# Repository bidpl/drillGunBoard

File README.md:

# 12V Motor Testing Rig

Code for FRC control board. Manual control FRC motors and air compressor.

We used 12v drills to power 12v FRC motors, (CIMs, BAGs, etc) by removing drill spindle and connecting to motor leads. However, it can not supply large amounts of power. It can not drive Neo motors due to their brushless nature. 

This code is for a meant for a test rig that take a pot input and controls PWM motor controlers (Talon SRXs and Spark Maxes are used in this build).

Features:
Control multiple motors (up to 4) (Control moudes v1.1 and v1.2 have support for 5)
LCD readout for motor power

Documentation is a bit scuffed, I only used the repo while developing the first version (v1.0), didn't for later iterations (v1.1/1.2)

v1.0 was based on an arduino uno with regular potentiometers. The arduino by itself was limited to Talon SRXs since it could not generate a stable enough PWM signal for the Spark Max. This version used regular pin headers and cheap dupont wires so it suffered some durability issues (connections were terrible, shaking the testing rig could disconnect parts).

v1.1/1.2 is uses a custom control module (based on an ATMEGA32P, programs exactly like an UNO) that has an additional PWM driver chip (PCA9685). This chip can generate a proper 50hz PWM signal so it can control Spark Maxes as well. This version also uses locking connectors (JST-XH between input modules and the control module, Molex SL connectors for control module to motor controllers).

## PCB Modules

## Testing Rig (The Bomb, name inspired from Die Hard with a Vengeance)

## Change Log
Input Module v1.1:
- Switched from rotate to linear potentiometer
- Switched from horizontal to vertical PCB shape

Control Module v1.2:
- Fixed PCA9685 CE signal (supposed to be active low, was tied high in prev version)

Control Module v1.1:
- Moved from arduino to custom PCB
- Added PCA9685 as PWM signal generator, arduino couldn't get a clean enough PWM signal for some motor controllers (Controlling the LCD delayed the signal too much)
- Switched from loose dupont wire to locking Molex-SL and JST-XH connectors

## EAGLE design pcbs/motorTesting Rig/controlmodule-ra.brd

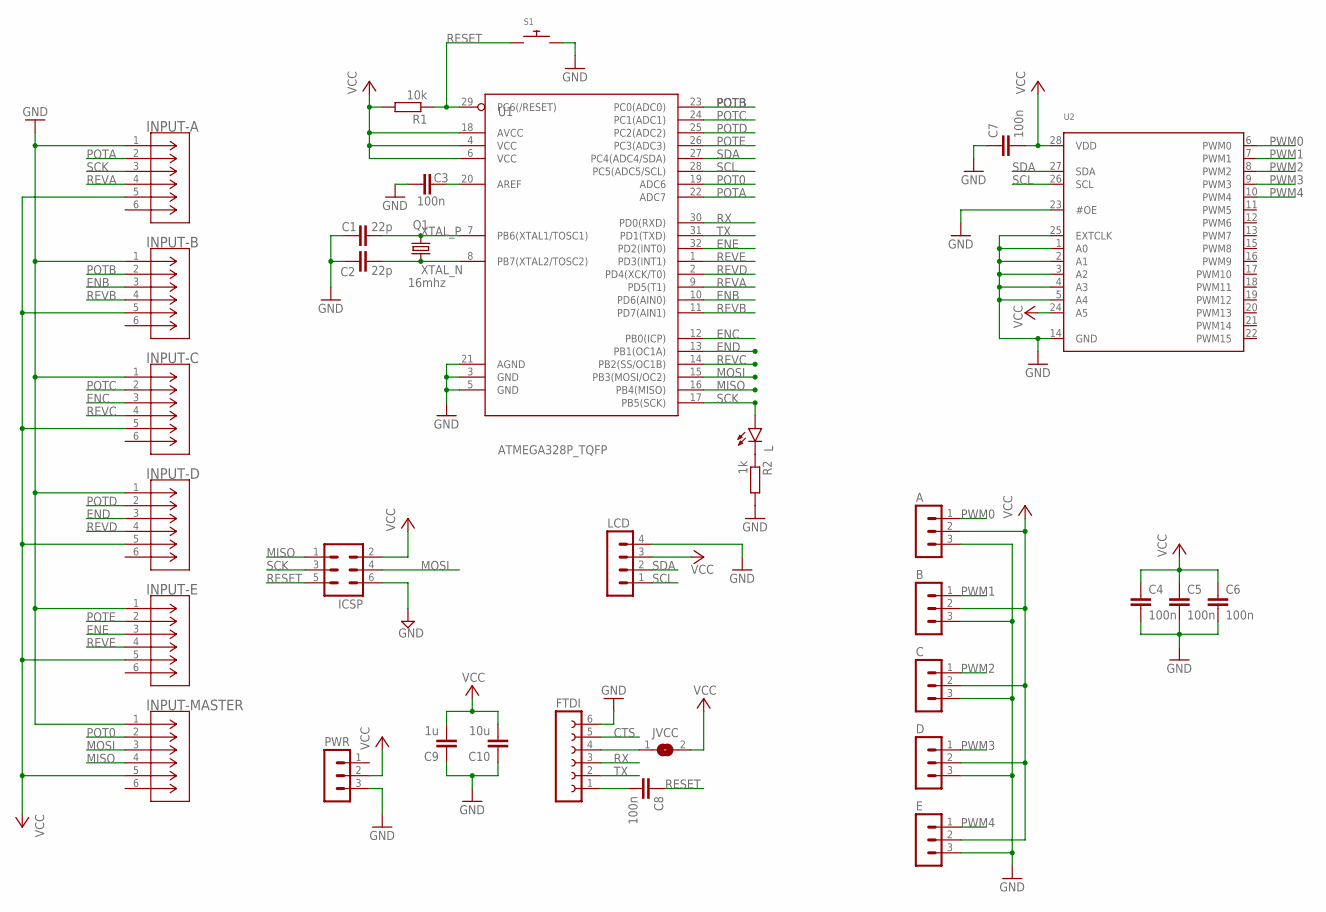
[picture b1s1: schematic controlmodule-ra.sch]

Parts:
A: MOLEX-SL-3PIN-RA-BOARD-LOCK
B: MOLEX-SL-3PIN-RA-BOARD-LOCK
C: MOLEX-SL-3PIN-RA-BOARD-LOCK
C1, C2: 22p; C0805
C3, C4, C5, C6, C7, C8: 100n; C0805
C9: 1u; C0805
C10: 10u; C0805
D: MOLEX-SL-3PIN-RA-BOARD-LOCK
E: MOLEX-SL-3PIN-RA-BOARD-LOCK
FTDI: FE06-1; FE06
ICSP: MA03-2
INPUT-A: B6B-PH-K-S(LF)(SN)-JST; CONN_B6B-PH-K-S_JST
INPUT-B: B6B-PH-K-S(LF)(SN)-JST; CONN_B6B-PH-K-S_JST
INPUT-C: B6B-PH-K-S(LF)(SN)-JST; CONN_B6B-PH-K-S_JST
INPUT-D: B6B-PH-K-S(LF)(SN)-JST; CONN_B6B-PH-K-S_JST
INPUT-E: B6B-PH-K-S(LF)(SN)-JST; CONN_B6B-PH-K-S_JST
INPUT-MASTER: B6B-PH-K-S(LF)(SN)-JST; CONN_B6B-PH-K-S_JST
JVCC: SJ
L: LEDCHIP-LED0805; CHIP-LED0805
LCD: MOLEX-SL-4PIN-RA-BOARD-LOCK
PWR: MOLEX-SL-3PIN-RA-BOARD-LOCK
Q1: 16mhz; HC49UP
R1: 10k; R0805
R2: 1k; R0805
S1: 3X4MM-PUHSBUTTON; 3X4MM-PUSHBUTTON
U1: ATMEGA328P_TQFP; TQFP32-08
U2: PCA9685; TSSOP28

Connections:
CTS: FTDI.5
ENB: INPUT-B.3, U1.10 (PD6(AIN0))
ENC: INPUT-C.3, U1.12 (PB0(ICP))
END: INPUT-D.3, U1.13 (PB1(OC1A))
ENE: INPUT-E.3, U1.32 (PD2(INT0))
GND: A.3, B.3, C.3, C1.1, C2.1, C3.2, C4.2, C5.2, C6.2, C7.1, C9.1, C10.1, D.3, E.3, FTDI.6, ICSP.6, INPUT-A.1, INPUT-B.1, INPUT-C.1, INPUT-D.1, INPUT-E.1, INPUT-MASTER.1, LCD.4, PWR.3, R2.2, S1.P$2, U1.3 (GND), U1.5 (GND), U1.21 (AGND), U2.1 (A0), U2.2 (A1), U2.3 (A2), U2.4 (A3), U2.5 (A4), U2.14 (GND), U2.23 (#OE), U2.25 (EXTCLK)
MISO: ICSP.1, INPUT-MASTER.4, U1.16 (PB4(MISO))
MOSI: ICSP.4, INPUT-MASTER.3, U1.15 (PB3(MOSI/OC2))
unnamed: FTDI.4, JVCC.1
unnamed: L.C, R2.1
unnamed: C3.1, U1.20 (AREF)
unnamed: C8.2, FTDI.1
POT0: INPUT-MASTER.2, U1.19 (ADC6)
POTA: INPUT-A.2, U1.22 (ADC7)
POTB: INPUT-B.2, U1.23 (PC0(ADC0))
POTC: INPUT-C.2, U1.24 (PC1(ADC1))
POTD: INPUT-D.2, U1.25 (PC2(ADC2))
POTE: INPUT-E.2, U1.26 (PC3(ADC3))
PWM0: A.1, U2.6 (PWM0)
PWM1: B.1, U2.7 (PWM1)
PWM2: C.1, U2.8 (PWM2)
PWM3: D.1, U2.9 (PWM3)
PWM4: E.1, U2.10 (PWM4)
RESET: C8.1, ICSP.5, R1.1, S1.P$1, U1.29 (PC6(/RESET))
REVA: INPUT-A.4, U1.9 (PD5(T1))
REVB: INPUT-B.4, U1.11 (PD7(AIN1))
REVC: INPUT-C.4, U1.14 (PB2(SS/OC1B))
REVD: INPUT-D.4, U1.2 (PD4(XCK/T0))
REVE: INPUT-E.4, U1.1 (PD3(INT1))
RX: FTDI.3, U1.30 (PD0(RXD))
SCK: ICSP.3, INPUT-A.3, L.A, U1.17 (PB5(SCK))
SCL: LCD.1, U1.28 (PC5(ADC5/SCL)), U2.26 (SCL)
SDA: LCD.2, U1.27 (PC4(ADC4/SDA)), U2.27 (SDA)
TX: FTDI.2, U1.31 (PD1(TXD))
VCC: A.2, B.2, C.2, C4.1, C5.1, C6.1, C7.2, C9.2, C10.2, D.2, E.2, ICSP.2, INPUT-A.5, INPUT-B.5, INPUT-C.5, INPUT-D.5, INPUT-E.5, INPUT-MASTER.5, JVCC.2, LCD.3, PWR.2, R1.2, U1.4 (VCC), U1.6 (VCC), U1.18 (AVCC), U2.24 (A5), U2.28 (VDD)
XTAL_N: C2.2, Q1.1, U1.8 (PB7(XTAL2/TOSC2))
XTAL_P: C1.2, Q1.2, U1.7 (PB6(XTAL1/TOSC1))

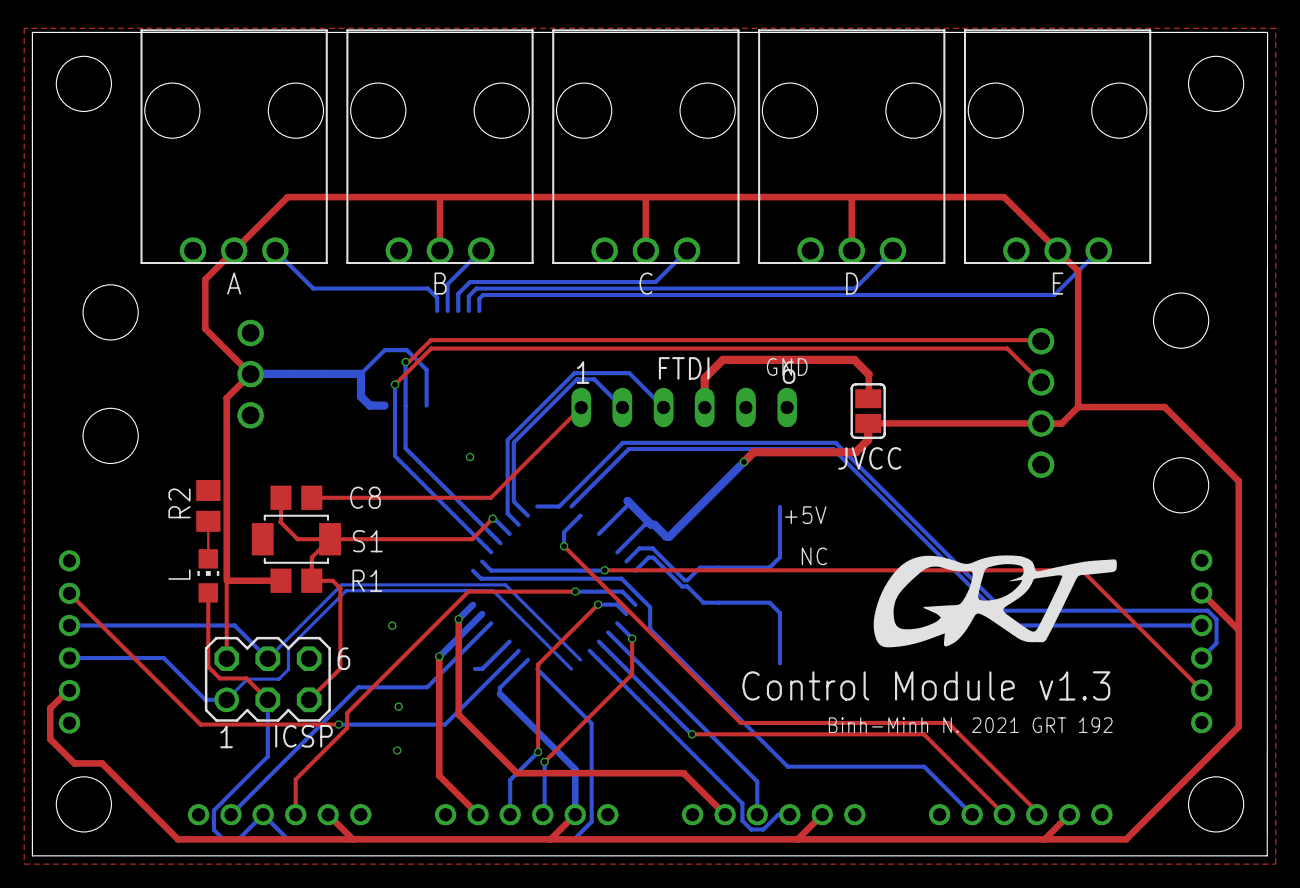
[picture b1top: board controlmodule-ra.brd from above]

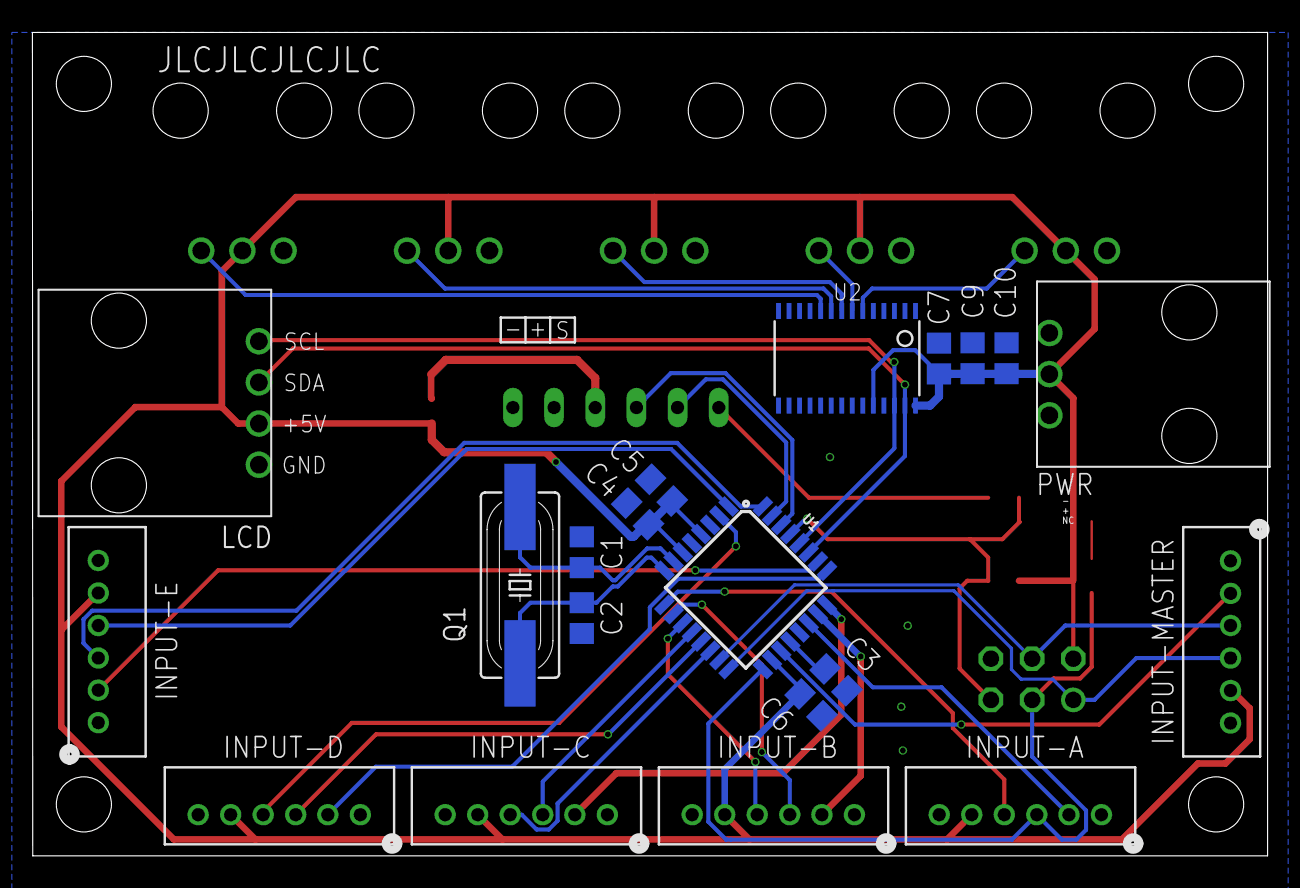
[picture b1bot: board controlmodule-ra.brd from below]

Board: 2 copper layers, 76.2 x 50.8 mm, 33 parts (20 on the bottom side), 36 nets.

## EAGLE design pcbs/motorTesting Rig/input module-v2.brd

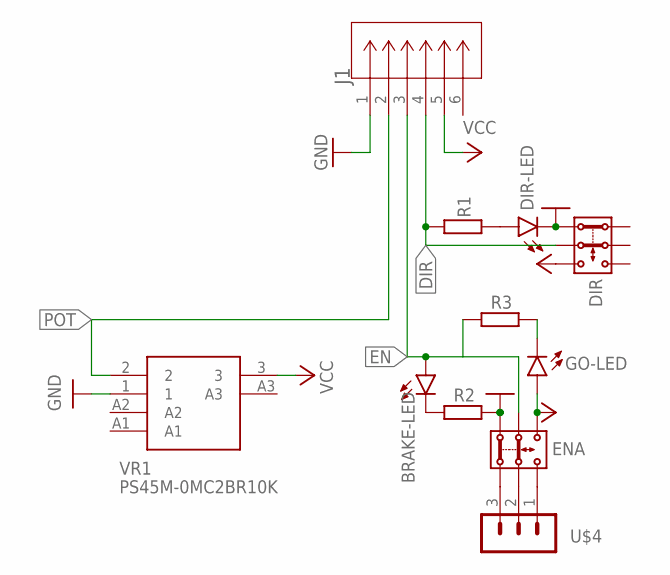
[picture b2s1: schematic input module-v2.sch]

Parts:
BRAKE-LED: LED5MM
DIR: DPDT-PUSHBUTTON; 7MM*7MM
DIR-LED: LED5MM
ENA: DPDT-PUSHBUTTON; 7MM*7MM
GO-LED: LED5MM
J1: B6B-PH-K-S(LF)(SN)-JST; CONN_B6B-PH-K-S_JST
R1, R2, R3: R-EU_0207/10; 0207/10
U$4: MALE-HEADER-3PIN; MA03-1
VR1: PS45M-0MC2BR10K; PS45M0MC2BR10K

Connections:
DIR: DIR.2, J1.4, R1.1
EN: BRAKE-LED.A, ENA.5, J1.3, R3.1
GND: DIR.1, DIR-LED.K (C), ENA.6, J1.1, R2.2, VR1.1
unnamed: DIR-LED.A, R1.2
unnamed: ENA.3, U$4.1
unnamed: ENA.2, U$4.2
unnamed: ENA.1, U$4.3
unnamed: BRAKE-LED.K (C), R2.1
unnamed: GO-LED.K (C), R3.2
POT: J1.2, VR1.2
VCC: DIR.3, ENA.4, GO-LED.A, J1.5, VR1.3

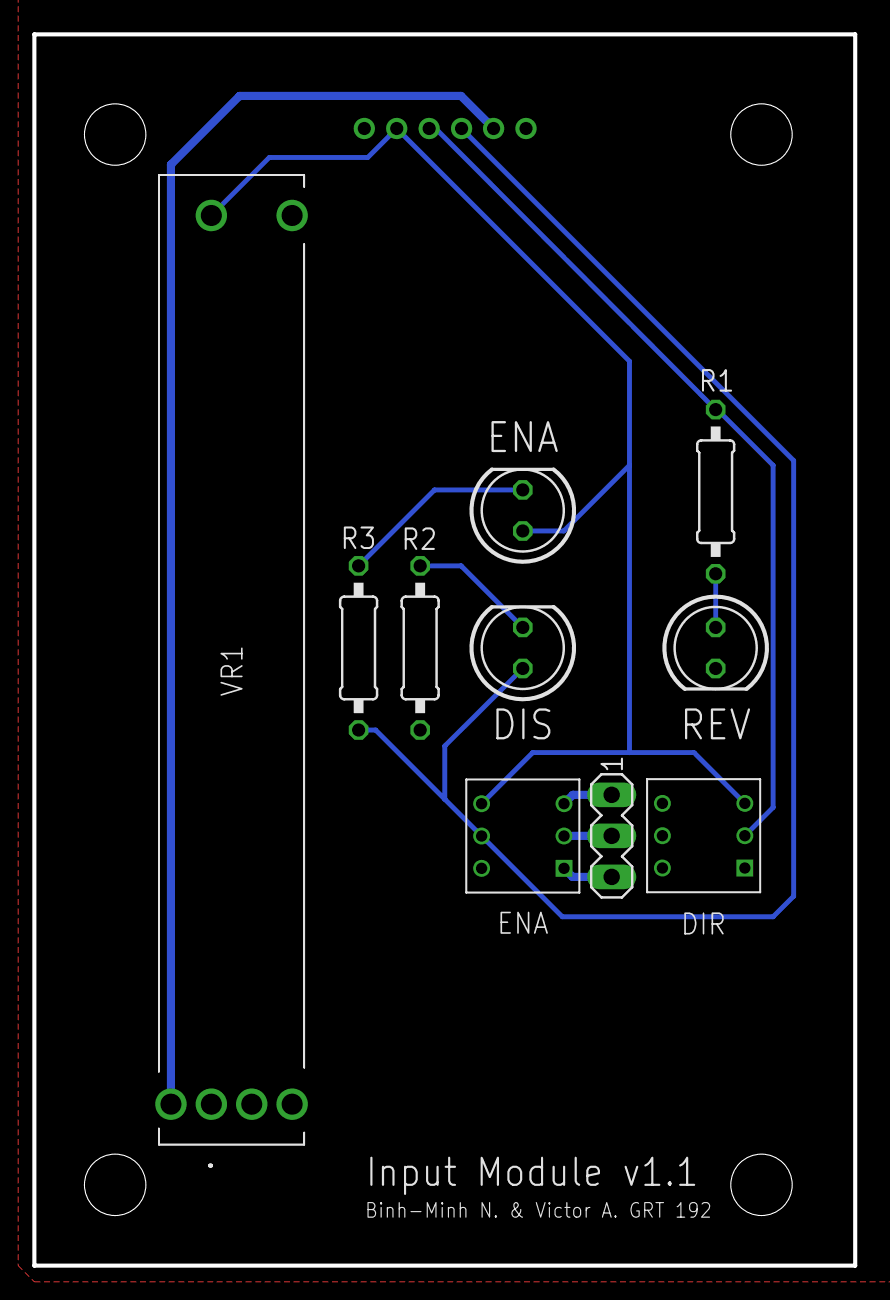
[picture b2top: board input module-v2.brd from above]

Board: 2 copper layers, 50.8 x 76.2 mm, 11 parts (1 on the bottom side), 11 nets.

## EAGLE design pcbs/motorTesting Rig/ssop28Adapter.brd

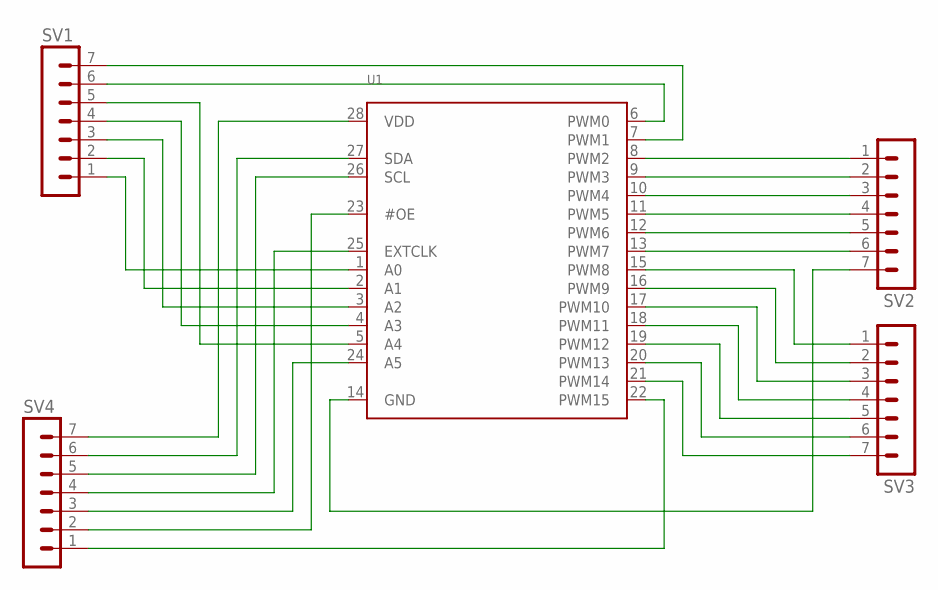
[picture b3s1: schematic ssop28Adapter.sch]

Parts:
SV1, SV2, SV3, SV4: MA07-1
U1: PCA9685; TSSOP28

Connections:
unnamed: SV1.1, U1.1 (A0)
unnamed: SV1.2, U1.2 (A1)
unnamed: SV1.3, U1.3 (A2)
unnamed: SV1.4, U1.4 (A3)
unnamed: SV1.5, U1.5 (A4)
unnamed: SV1.6, U1.6 (PWM0)
unnamed: SV1.7, U1.7 (PWM1)
unnamed: SV2.1, U1.8 (PWM2)
unnamed: SV2.2, U1.9 (PWM3)
unnamed: SV2.3, U1.10 (PWM4)
unnamed: SV2.4, U1.11 (PWM5)
unnamed: SV2.5, U1.12 (PWM6)
unnamed: SV2.6, U1.13 (PWM7)
unnamed: SV2.7, U1.14 (GND)
unnamed: SV3.1, U1.15 (PWM8)
unnamed: SV3.2, U1.16 (PWM9)
unnamed: SV3.3, U1.17 (PWM10)
unnamed: SV3.4, U1.18 (PWM11)
unnamed: SV3.5, U1.19 (PWM12)
unnamed: SV3.6, U1.20 (PWM13)
unnamed: SV3.7, U1.21 (PWM14)
unnamed: SV4.1, U1.22 (PWM15)
unnamed: SV4.2, U1.23 (#OE)
unnamed: SV4.3, U1.24 (A5)
unnamed: SV4.4, U1.25 (EXTCLK)
unnamed: SV4.5, U1.26 (SCL)
unnamed: SV4.6, U1.27 (SDA)
unnamed: SV4.7, U1.28 (VDD)

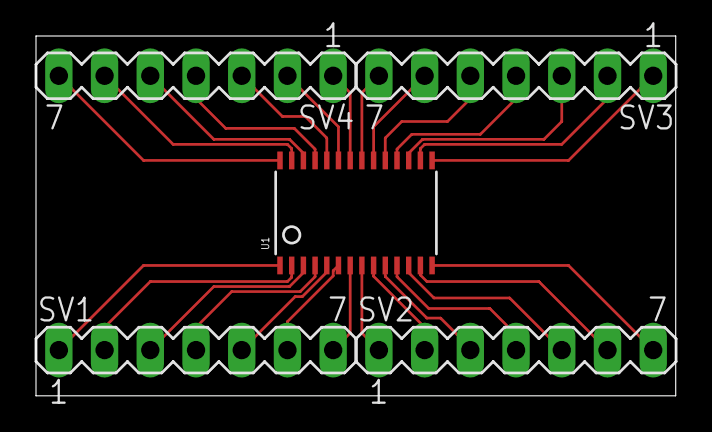
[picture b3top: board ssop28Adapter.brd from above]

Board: 2 copper layers, 35.5 x 20.0 mm, 5 parts (0 on the bottom side), 28 nets.

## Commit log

2019-05-07 Updated READEME.md, created arduino project file. Added code for LCD control and Joystick input
2019-07-14 now drives PWM motor controller and potentiometer support
2020-01-08 Redid stuff, now works with the Not Bomb tm. Use lcdTiming.ino, B and C are switched from physical order
2021-12-26 Added code for The Bomb and commented it
2021-12-26 Added EAGLE files, line endings might be a bit messed up in that folder
2022-01-18 Added images and edited README.md
2023-12-27 control board v1.3, moved stuff to bottom side to avoid aluminum shavings

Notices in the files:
parts and their libraries:
COPYRIGHT: Copyright (C) 2018 Accelerated Designs. All rights reserved
